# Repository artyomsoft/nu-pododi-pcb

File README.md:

# "Nu, Pogodi!" KiCAD project

## Description

This repository contains KiCAD project for the "Nu, Pogodi!" emulator.

## Intructions 

The repository includes a submodule. To clone it you must use the following command

~~~
git clone --recurse-submodules https://github.com/artyomsoft/nu-pododi-pcb.git
~~~

## Contents of the repository

**Shematic**

**Layout**

**Wiring**

[Interactive BOM](https://html-preview.github.io/?url=https://raw.githubusercontent.com/artyomsoft/nu-pododi-pcb/refs/heads/master/bom/ibom.html)

## Usefull links

1. [Firmware for the emulator](https://github.com/artyomsoft/pico-nu-pogodi)
2. [3D Models of the case](https://github.com/artyomsoft/nu-pogodi-case)
3. [These 3D Models ready for printing on MakerWorld](https://makerworld.com/en/models/1602053-nu-pogodi-game-emulator)

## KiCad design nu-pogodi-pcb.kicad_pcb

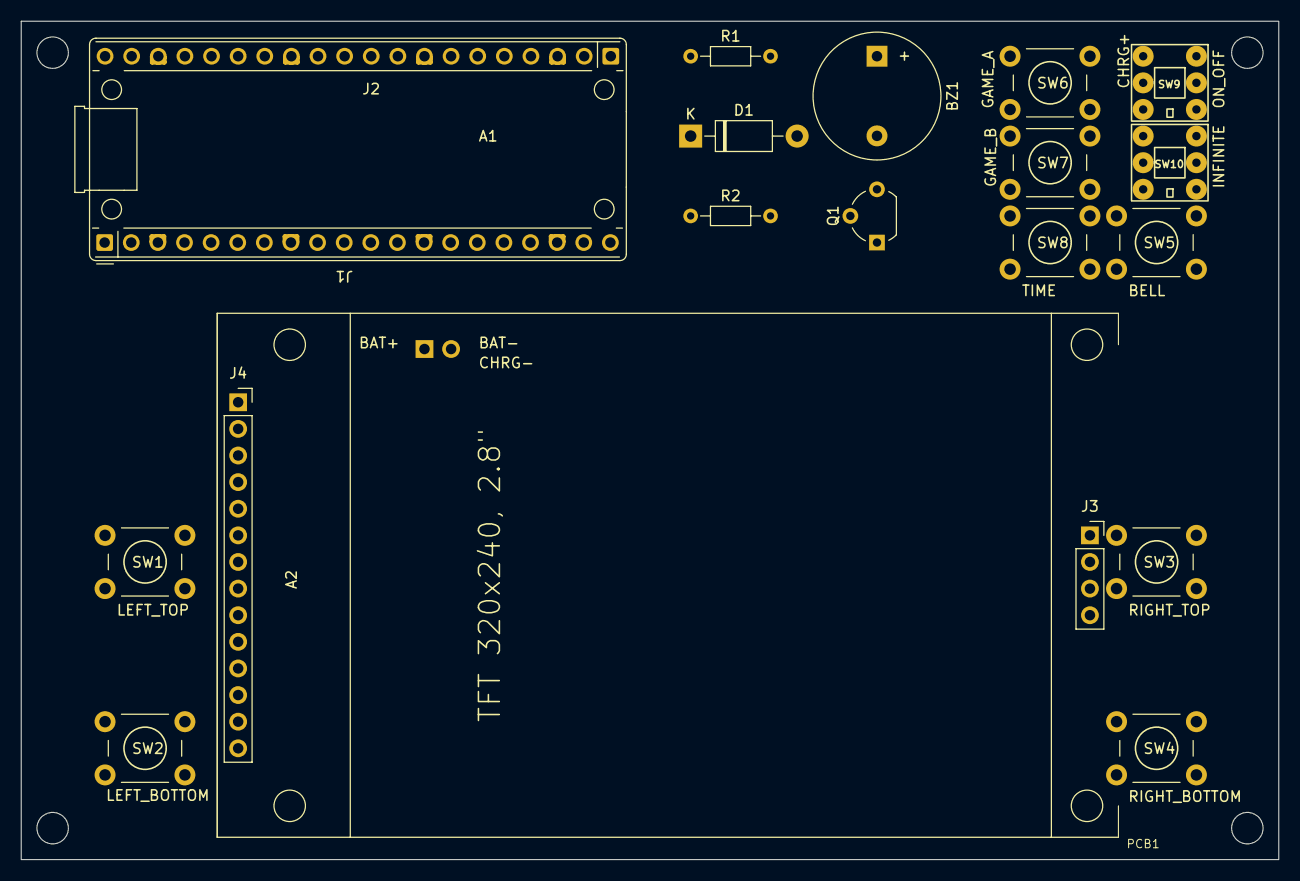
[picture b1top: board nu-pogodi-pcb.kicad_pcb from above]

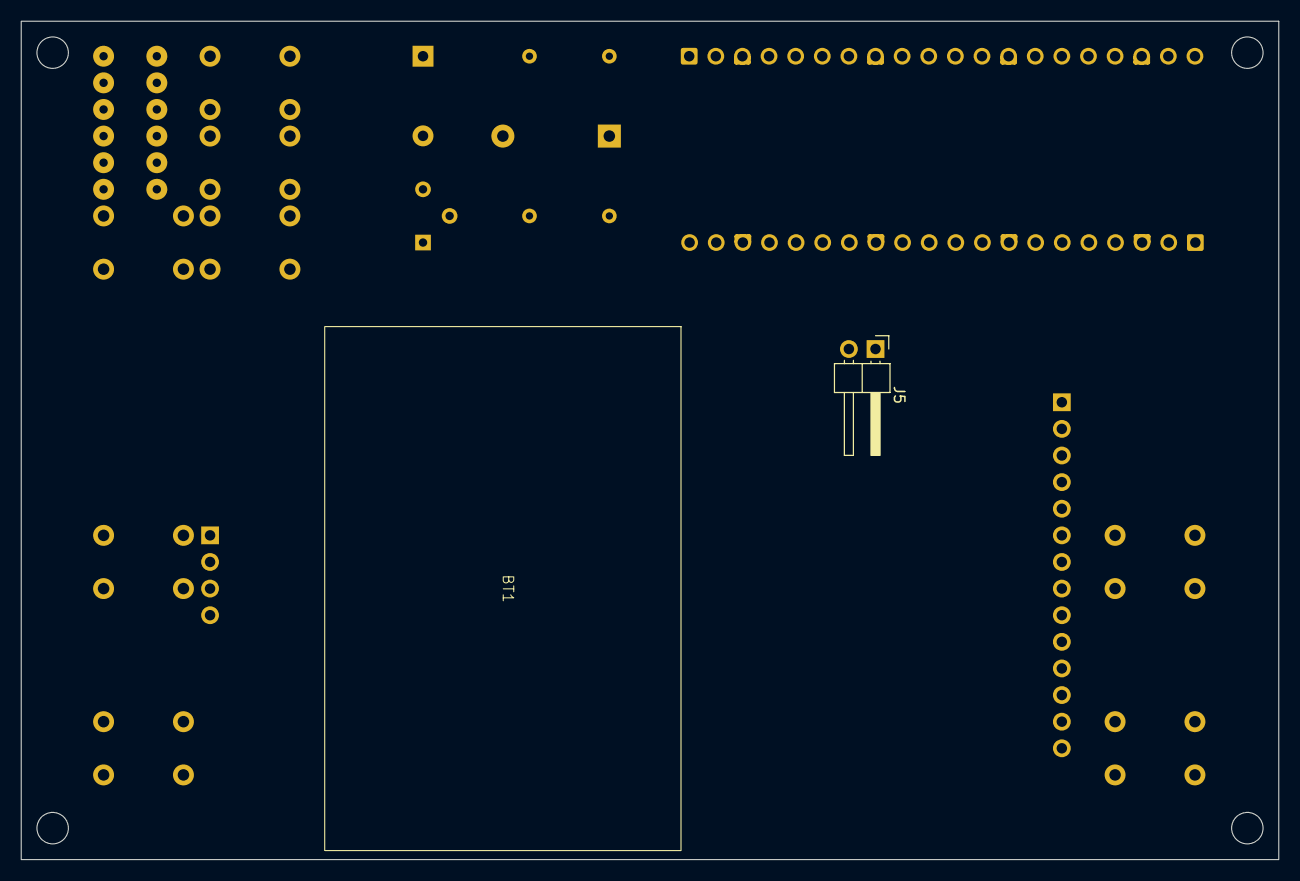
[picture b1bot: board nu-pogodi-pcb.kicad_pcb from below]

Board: 10 copper layers, 120.0 x 80.0 mm, 24 parts (2 on the bottom side), 20 nets.

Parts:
A1: RaspberryPi_Pico; RaspberryPi_Pico_Original_Virtual
A2: MSP2806; MSP_2807
BT1: Li-Po Battery 503450; LI-Po 503450
BZ1: Buzzer; Buzzer_12x9.5RM7.6
D1: 1N5819; D_DO-41_SOD81_P10.16mm_Horizontal
J1: Pico_Socket_A; RaspberryPi_Pico_PinSocket_1x20_P2.54mm_Vertical
J2: Pico_Socket_B; RaspberryPi_Pico_PinSocket_1x20_P2.54mm_Vertical
J3: MSP2806 Socket A; MSP_2807_Socket_A
J4: MSP2806 Socket B; MSP_2807_Socket_B
J5: Conn_01x02_Pin; PinHeader_1x02_P2.54mm_Horizontal
PCB1: Perfboard 120x80; Perfboard_120x80mm_1260_Holes
Q1: 2N2222; TO-92_Wide
R1: 1K; R_Axial_DIN0204_L3.6mm_D1.6mm_P7.62mm_Horizontal
R2: 100; R_Axial_DIN0204_L3.6mm_D1.6mm_P7.62mm_Horizontal
SW1, SW2, SW3, SW4, SW5, SW6, SW7, SW8: SPST-NO 6x6mm; SW_PUSH_BB_6mm
SW9, SW10: SW_DPDT_x2; SW_DPDT_XLX

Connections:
+3V3: J2.16 (3V3), J4.1 (VCC), J4.8 (LED), R2.1, SW10.2 (B)
/BUZZER: J1.20 (GPIO15), R1.1
/COL_1: J1.14 (GPIO10), SW1.2, SW5.2
/COL_2: J1.15 (GPIO11), SW2.2, SW6.2
/COL_3: J1.16 (GPIO12), SW3.2, SW7.2
/COL_4: J1.17 (GPIO13), SW4.2, SW8.2
/CS: J2.2 (GPIO17), J4.3 (CS)
/D/C: J2.7 (GPIO21), J4.5 (D/C)
/INFINITE: J1.11 (GPIO8), SW10.3 (C)
/MOSI: J2.5 (GPIO19), J4.6 (SDI(MOSI))
/ROW_1: J1.10 (GPIO7), SW1.1, SW2.1, SW3.1, SW4.1
/ROW_2: J1.9 (GPIO6), SW5.1, SW6.1, SW7.1, SW8.1
/RST: J2.6 (GPIO20), J4.4 (RESET)
/SCK: J2.4 (GPIO18), J4.7 (SCK)
/VSYS: D1.1 (K), J2.19 (VSYS)
GND: J1.3 (GND), J1.8 (GND), J1.13 (GND), J1.18 (GND), J2.3 (GND), J2.8 (GND), J2.18 (GND), J4.2 (GND), J5.2, Q1.1 (E)
unnamed: BZ1.1 (+), R2.2
unnamed: BZ1.2 (-), Q1.3 (C)
unnamed: D1.2 (A), SW9.3 (C)
unnamed: Q1.2 (B), R1.2

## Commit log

2025-07-13 Added Kicad project
2025-08-03 Fixed pinout
